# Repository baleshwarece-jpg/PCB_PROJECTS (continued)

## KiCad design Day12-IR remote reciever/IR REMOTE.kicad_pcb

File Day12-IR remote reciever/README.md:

IR Remote Receiver Module
Infrared signal reception interface for wireless remote control and embedded automation systems
The IR Remote Receiver Module is a compact PCB designed to receive and decode infrared signals transmitted by standard consumer remote controls. Built around a 38 kHz demodulating IR receiver, the board converts modulated infrared light into clean digital pulses that can be processed by microcontrollers and embedded systems.

This project introduces wireless communication fundamentals, infrared signal detection, noise filtering, power supply decoupling, and sensor interfacing techniques commonly used in consumer electronics.

Designed in KiCad, the module serves as a reusable building block for home automation systems, smart appliances, robotics, media controllers, and custom embedded user interfaces.

How It Works

A handheld IR remote transmits commands by modulating infrared light at a carrier frequency, typically 38 kHz. The IR receiver detects this modulated light through its photodiode and internal signal-processing circuitry.

The receiver automatically filters ambient light interference, amplifies the incoming signal, and demodulates the 38 kHz carrier to produce a clean digital output waveform.

This output can be connected directly to a microcontroller GPIO pin, where firmware interprets the pulse timings to identify specific remote-control commands and user inputs.

A local decoupling capacitor stabilizes the receiver supply voltage and improves immunity to electrical noise.

Bill of Materials
Reference	Value	Description	KiCad Symbol	Footprint
U1	VS1838B / TSOP38238	Infrared receiver module	Sensor_Optical:IR_Receiver	SIP-3
C1	100 nF	Supply decoupling capacitor	Device:C	C_0805
C2	10 µF	Power filtering capacitor	Device:CP	CP_Radial
J1	3-Pin Header	Power and signal connector	Connector_Generic:Conn_01x03	PinHeader_1x03
H1-H2	Mounting Holes	Mechanical support	Mechanical:MountingHole	MountingHole_3.2mm
Electrical Specifications
Parameter	Value
Operating Voltage	2.7 V – 5.5 V
Typical Supply Voltage	5 V
Carrier Frequency	38 kHz
Output Type	Active-Low Digital Signal
Detection Range	Up to 8–10 m
Viewing Angle	±45° Typical
PCB Type	Two-Layer FR4
Header Pitch	2.54 mm
Schematic

Designed using KiCad 7.

Repository contents include:

Schematic: hardware/ir_remote_receiver.kicad_sch
PCB Layout: hardware/ir_remote_receiver.kicad_pcb
Gerber Files: hardware/gerbers/
BOM: hardware/bom.csv

The design passes ERC validation and follows manufacturer-recommended filtering and power supply guidelines.

Design Notes
Why Use a Demodulating Receiver?

Raw infrared photodiodes are highly sensitive to ambient light and electrical noise. A demodulating receiver integrates filtering, amplification, automatic gain control, and carrier detection, providing a clean digital signal suitable for direct microcontroller interfacing.

Power Supply Filtering

IR receiver modules contain sensitive analog amplification stages. Both 100 nF and 10 µF capacitors are included to suppress supply noise and ensure stable operation in electrically noisy environments.

38 kHz Compatibility

Most consumer electronics—including televisions, air conditioners, audio systems, and media players—use 38 kHz IR carriers. Designing around this frequency maximizes compatibility with commercially available remotes.

Compact Sensor Module Architecture

By separating the IR receiver into a dedicated PCB, the module can be reused across multiple projects without redesigning the infrared interface circuitry each time.

Learning Outcomes

This project provides practical experience with:

Infrared communication systems
Wireless command reception
Digital pulse decoding concepts
Sensor signal conditioning
Power supply filtering
Embedded user interface hardware
Getting Started
Open the project files using KiCad 7 or later.
Review the schematic and verify ERC results.
Generate fabrication files or use the supplied Gerbers.
Assemble the PCB according to the BOM.
Connect VCC, GND, and OUT to a microcontroller.
Upload an IR decoding program.
Point a compatible remote control at the receiver and monitor received commands.

The hardware requires external firmware for protocol decoding and command processing.

License

Released under the CERN Open Hardware Licence Version 2 – Permissive (CERN-OHL-P).

You are free to study, modify, manufacture, and distribute this design in accordance with the license terms.

References
VS1838B Datasheet
TSOP38238 Datasheet
Infrared Remote Communication Standards
KiCad Documentation
CERN Open Hardware Licence v2 (CERN-OHL-P)

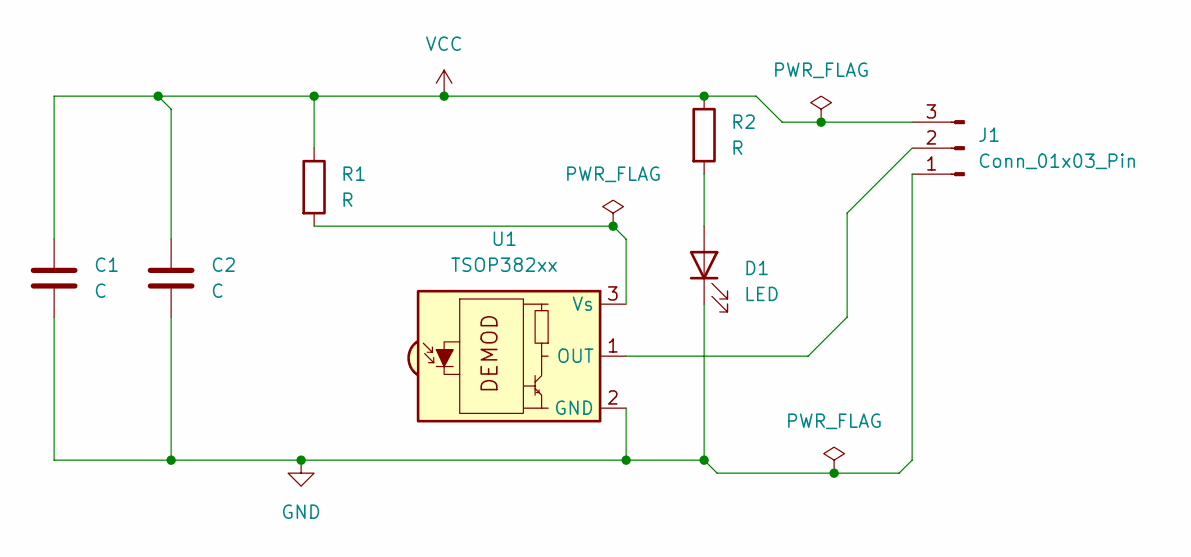
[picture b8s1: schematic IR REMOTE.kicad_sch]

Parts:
C1: C; CP_Radial_D6.3mm_P2.50mm
C2: C; C_Disc_D5.0mm_W2.5mm_P2.50mm
D1: LED; LED_D5.0mm
J1: Conn_01x03_Pin; TerminalBlock_MaiXu_MX126-5.0-03P_1x03_P5.00mm
R1, R2: R; R_Axial_DIN0207_L6.3mm_D2.5mm_P10.16mm_Horizontal
U1: TSOP382xx; Vishay_MINICAST-3Pin

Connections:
GND: C1.2, C2.2, D1.1 (K), J1.1, U1.2 (GND)
unnamed: D1.2 (A), R2.2
unnamed: J1.2, U1.1 (OUT)
unnamed: R1.2, U1.3 (Vs)
VCC: C1.1, C2.1, J1.3, R1.1, R2.1

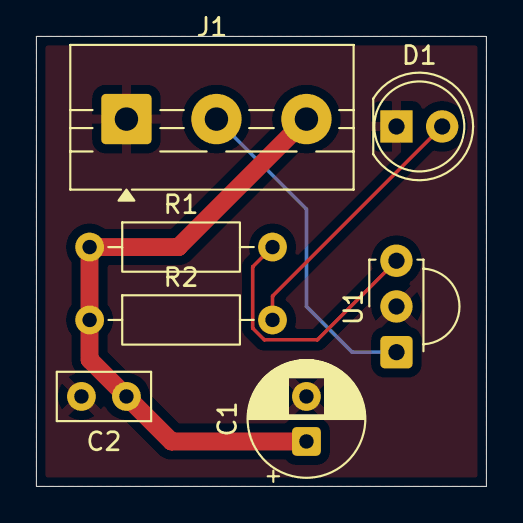
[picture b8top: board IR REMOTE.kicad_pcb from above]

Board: 2 copper layers, 25.0 x 25.0 mm, 7 parts (0 on the bottom side), 5 nets.
